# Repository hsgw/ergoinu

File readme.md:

Ergoinu
===

***An (Not Portable But Small) Ergonomic Split Keyboard.***

## Keyboard Maintainer
[Twitter @hsgw](https://twitter.com/hsgw)

## Software Supported
[QMK Firmware](https://github.com/qmk/qmk_firmware)   

## Build guide & tips
[wiki](https://github.com/hsgw/ergoinu/wiki)

## Buy
[shop](https://dm9.thebase.in/items/13093286)

## License
pcb and case designs are licensed under creative commons BY SA 4.0  
[https://creativecommons.org/licenses/by-sa/4.0/](https://creativecommons.org/licenses/by-sa/4.0/)   
(c) Takuya Urakawa (dm9recoreds.com)

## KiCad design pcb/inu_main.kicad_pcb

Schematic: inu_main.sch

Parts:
CON1, CON2: MJ-4PP-9
D1, D2, D3, D4, D5, D6, D7, D8, D9, D10, D11, D12, D13, D14, D15, D16, D17, D18, D19, D20, D21, D22, D23, D24, D25, D26, D27, D28, D29, D30, D31, D32, D33: 1N4148; D_SOD123_double_side
J1: Conn_01x01; Pin_Header_Straight_1x01_Pitch2.54mm
J2, J3: Conn_01x03; WS2812_tape_10mm
SILK1, SILK3: silk; logo_hsgw_7_5mm
SILK2, SILK4: silk; logo_dm9_15mm
SW1: TactSW_2pin; TVBP06
SW_MX1, SW_MX2, SW_MX3, SW_MX4, SW_MX5, SW_MX6, SW_MX7, SW_MX8, SW_MX9, SW_MX10, SW_MX11, SW_MX12, SW_MX13, SW_MX14, SW_MX15, SW_MX16, SW_MX17, SW_MX18, SW_MX19, SW_MX20, SW_MX21, SW_MX23, SW_MX24, SW_MX25, SW_MX26, SW_MX27, SW_MX28, SW_MX29, SW_MX31, SW_MX32, SW_MX33, SW_MX34: SW_Push; SW_Cherry_MX1A_1.00u_Plate_double_side
SW_MX22, SW_MX30: SW_Push; SW_Cherry_MX1A_1.75u_Plate_double_side
SW_MX35: SW_Push; SW_Cherry_MX1A_1.25u_Plate_double_side
U1: pro_micro; Pro_Micro_Reverse_silk

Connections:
+5V: CON1.2, CON2.2, J2.3, J3.3, U1.21
/COL0: SW_MX1.1, SW_MX8.1, SW_MX15.2, SW_MX22.2, SW_MX23.2, SW_MX30.2, U1.11
/COL1: SW_MX2.1, SW_MX9.1, SW_MX16.2, SW_MX24.2, U1.10
/COL2: SW_MX3.1, SW_MX10.1, SW_MX17.1, SW_MX25.1, SW_MX31.1, U1.9
/COL3: SW_MX4.1, SW_MX11.1, SW_MX18.1, SW_MX26.1, SW_MX32.1, U1.8
/COL4: SW_MX5.1, SW_MX12.1, SW_MX19.1, SW_MX27.1, SW_MX33.1, U1.7
/COL5: SW_MX6.1, SW_MX13.1, SW_MX20.1, SW_MX28.1, SW_MX34.1, U1.19
/COL6: SW_MX7.1, SW_MX14.1, SW_MX21.1, SW_MX29.1, SW_MX35.1, U1.20
/DATA: CON1.3, CON2.3, U1.2
/LED: J2.2, J3.2, U1.13
/RESET: SW1.1, U1.22
/ROW0: D1.1, D2.1, D3.1, D4.1, D5.1, D6.1, D7.1, U1.18
/ROW1: D8.1, D9.1, D10.1, D11.1, D12.1, D13.1, D14.1, U1.17
/ROW2: D15.1, D16.1, D17.1, D18.1, D19.1, D20.1, D21.1, U1.16
/ROW3: D22.1, D23.1, D24.1, D25.1, D26.1, D27.1, D28.1, U1.15
/ROW4: D29.1, D30.1, D31.1, D32.1, D33.1, U1.14
GND: CON1.1, CON2.1, J2.1, J3.1, SW1.2, U1.3, U1.4, U1.23
unnamed: CON1.4, CON2.4, J1.1
unnamed: D1.2, SW_MX1.2
unnamed: D2.2, SW_MX2.2
unnamed: D3.2, SW_MX3.2
unnamed: D4.2, SW_MX4.2
unnamed: D5.2, SW_MX5.2
unnamed: D6.2, SW_MX6.2
unnamed: D7.2, SW_MX7.2
unnamed: D8.2, SW_MX8.2
unnamed: D9.2, SW_MX9.2
unnamed: D10.2, SW_MX10.2
unnamed: D11.2, SW_MX11.2
unnamed: D12.2, SW_MX12.2
unnamed: D13.2, SW_MX13.2
unnamed: D14.2, SW_MX14.2
unnamed: D15.2, SW_MX15.1, SW_MX22.1
unnamed: D16.2, SW_MX16.1
unnamed: D17.2, SW_MX17.2
unnamed: D18.2, SW_MX18.2
unnamed: D19.2, SW_MX19.2
unnamed: D20.2, SW_MX20.2
unnamed: D21.2, SW_MX21.2
unnamed: D22.2, SW_MX23.1, SW_MX30.1
unnamed: D23.2, SW_MX24.1
unnamed: D24.2, SW_MX25.2
unnamed: D25.2, SW_MX26.2
unnamed: D26.2, SW_MX27.2
unnamed: D27.2, SW_MX28.2
unnamed: D28.2, SW_MX29.2
unnamed: D29.2, SW_MX31.2
unnamed: D30.2, SW_MX32.2
unnamed: D31.2, SW_MX33.2
unnamed: D32.2, SW_MX34.2
unnamed: D33.2, SW_MX35.2

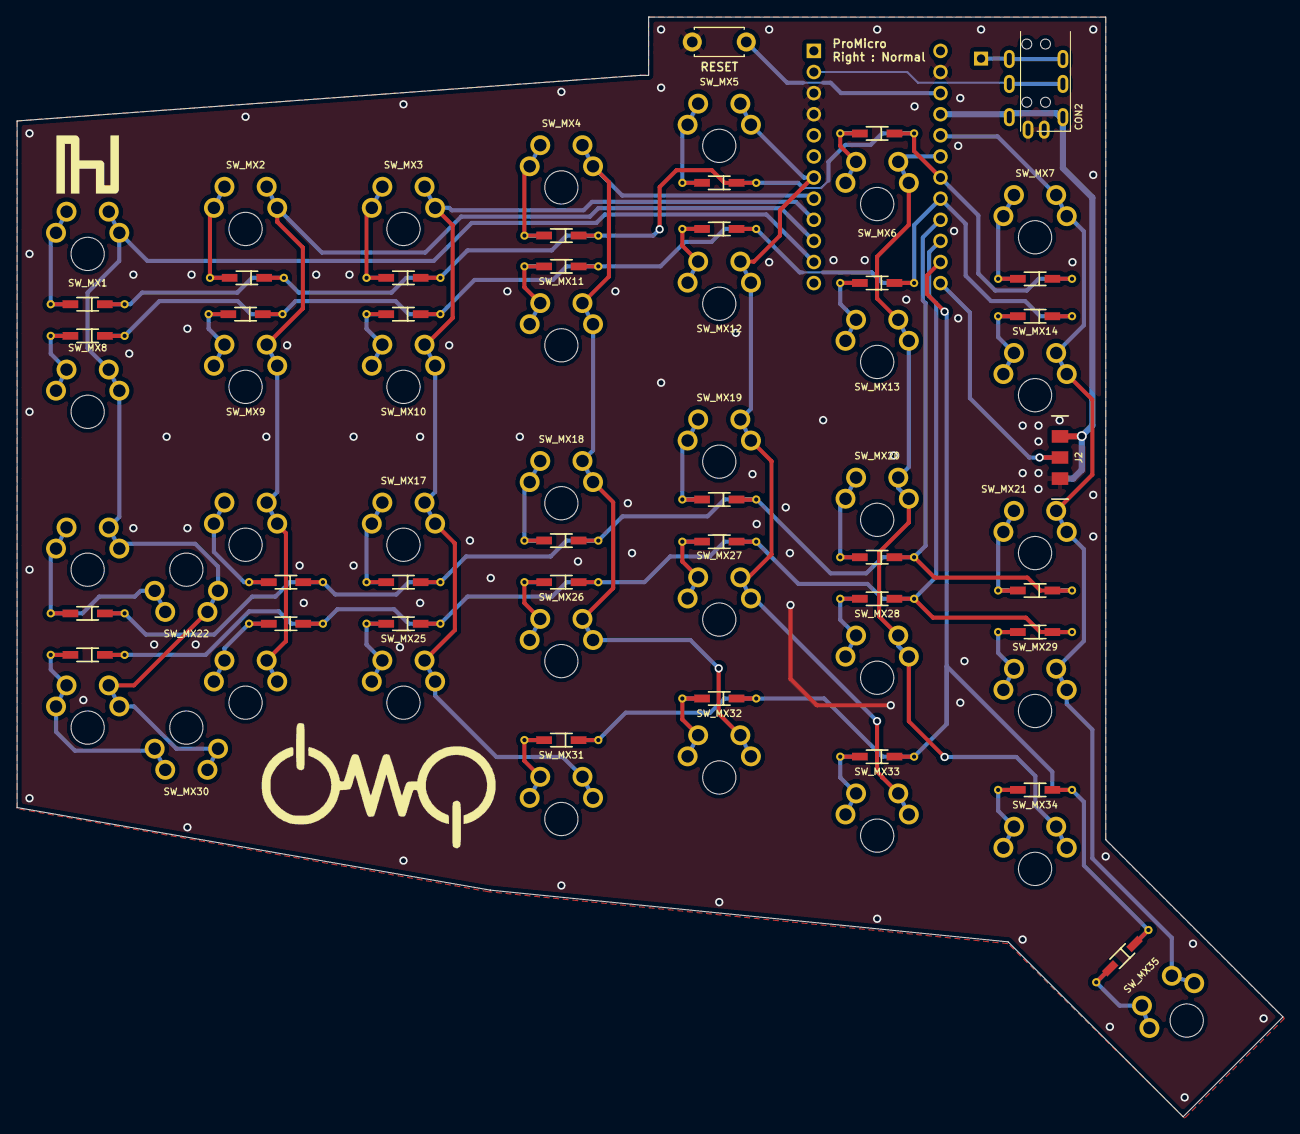
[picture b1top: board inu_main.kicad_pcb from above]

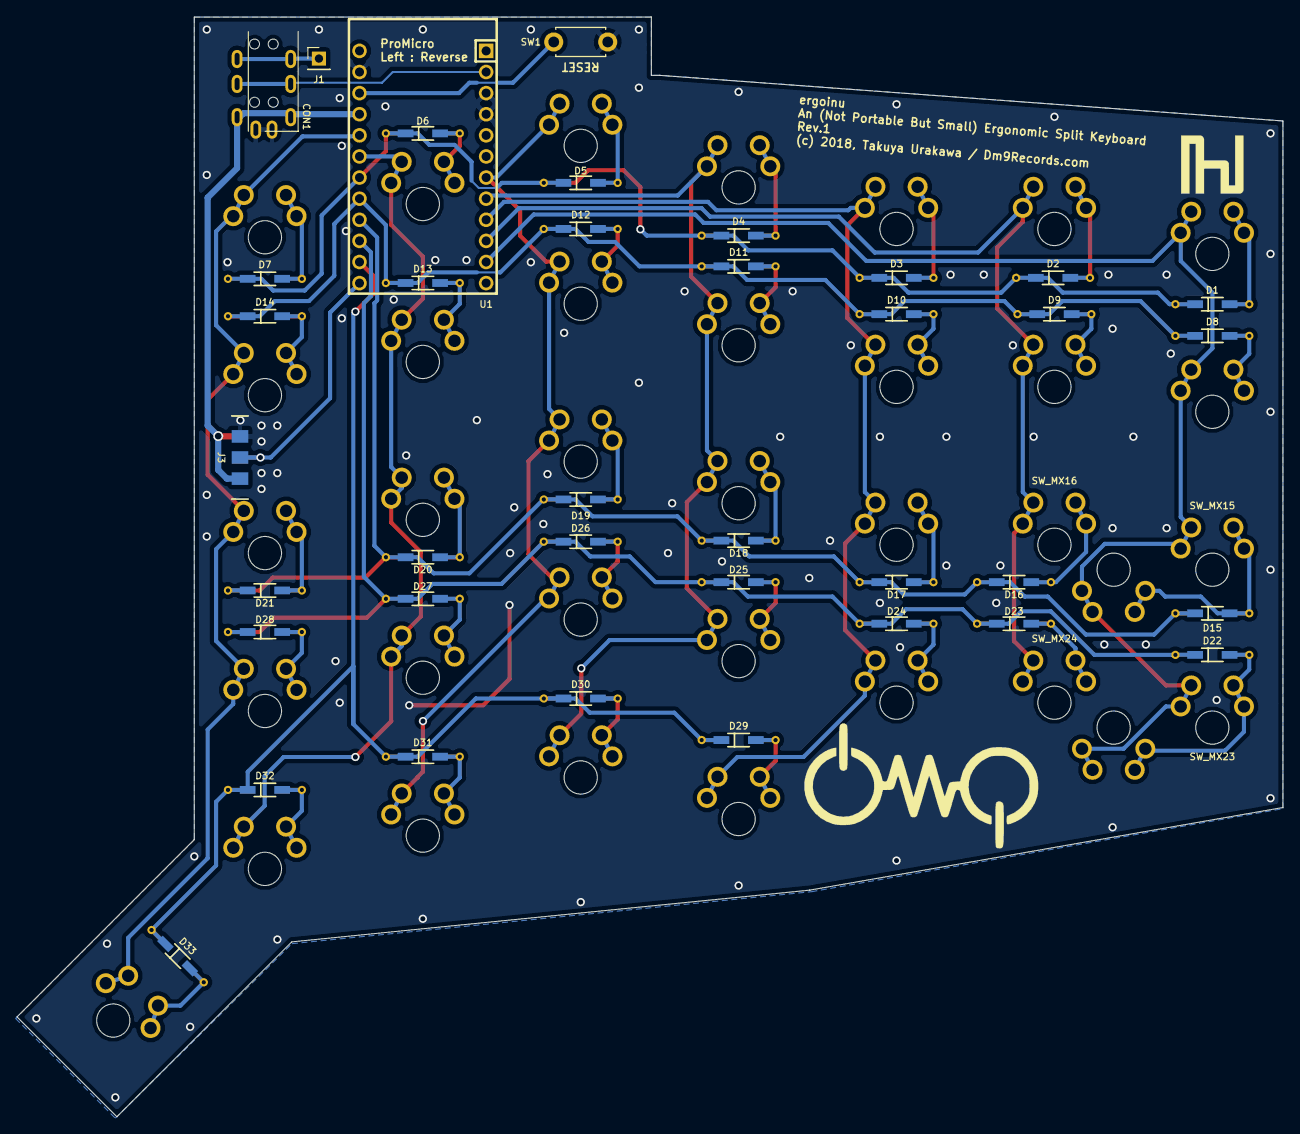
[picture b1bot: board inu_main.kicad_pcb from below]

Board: 2 copper layers, 152.3 x 132.3 mm, 79 parts (43 on the bottom side), 51 nets.

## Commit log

2018-08-11 1st commit
2018-08-11 add readme.md
2018-08-11 add image
2018-08-11 fix typo
2018-08-11 Create LICENSE
2018-08-12 add via to pcb
2018-08-12 fix silk on pcb
2018-08-12 add buildguide_jp.md
2018-08-21 add case design file
2018-08-21 remove fp-lib-table
2018-08-21 add before buy page update readme and buildguide
2018-08-22 fix link
2018-08-22 move documents
2018-08-22 Set theme jekyll-theme-minimal
2018-08-22 Set theme jekyll-theme-cayman
2018-08-22 fix table
2018-08-22 update gh pages
2018-08-22 change theme
2018-08-22 remove theme
2018-08-22 apply theme
2018-08-22 move doc to wiki
2018-08-22 update pcb
2018-08-27 add shop link
2018-08-27 update case file
2018-09-26 pcb rev 1 final update

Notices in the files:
pcb/inu_main.kicad_pcb:
(c) 2018, Takuya Urakawa / Dm9Records.com
